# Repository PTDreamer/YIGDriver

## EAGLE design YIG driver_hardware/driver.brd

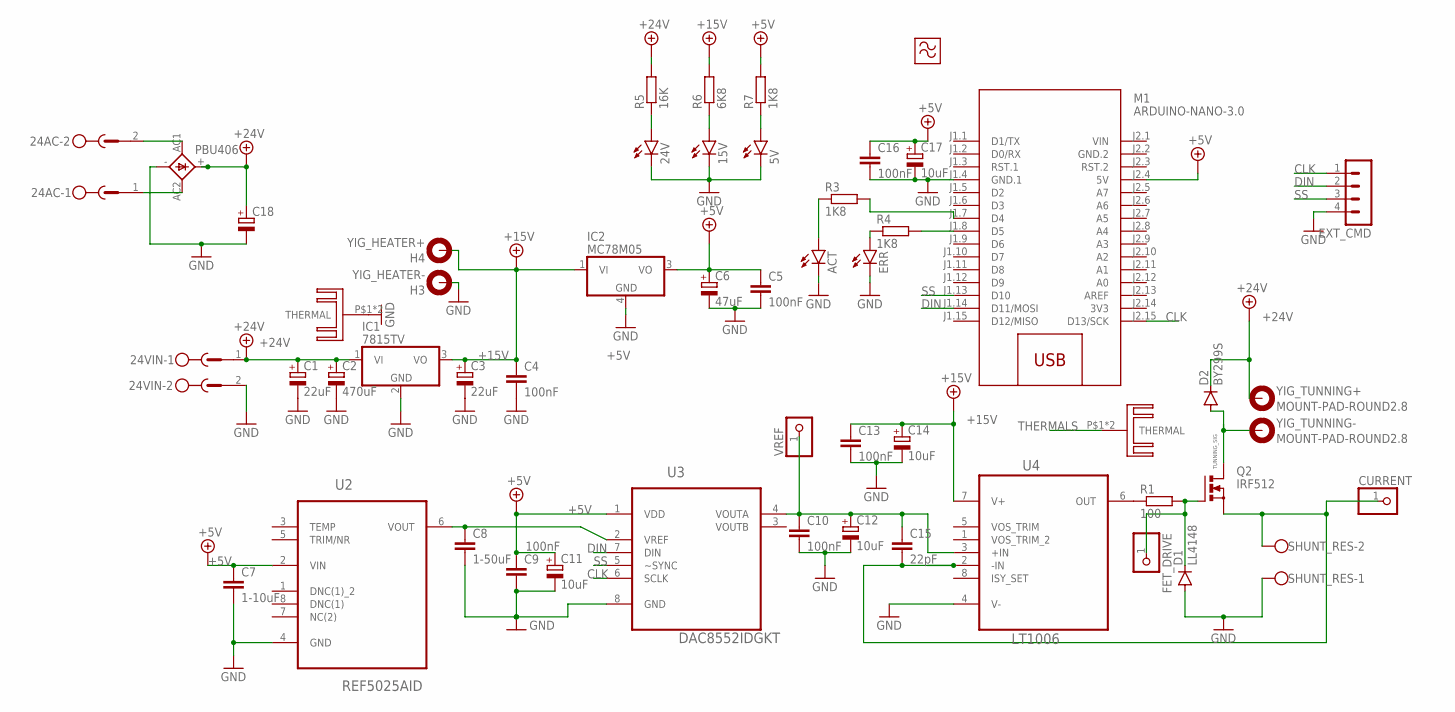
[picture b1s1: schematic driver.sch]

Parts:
5V, 15V, 24V: LEDCHIP-LED0805; CHIP-LED0805
24AC, 24VIN: MSTBV2
ACT: LEDCHIP-LED0805; CHIP-LED0805
C1, C3: 22uF; PANASONIC_E
C2: 470uF; E5-10,5
C4, C13: 100nF; C1210
C5, C9, C10, C16: 100nF; C0603K
C6: 47uF; PANASONIC_D
C7: 1-10uF; C3216
C8: 1-50uF; C3216
C11, C12, C17: 10uF; A/3216-18R
C14: 10uF; E2,5-5
C15: 22pF; C0603
C18: CPOL-EUE7.5-18; E7,5-18
CURRENT: PINHD-1X1; 1X01
D1: LL4148; SOD80C
D2: BY299S; D-10
ERR: LEDCHIP-LED0805; CHIP-LED0805
EXT_CMD: MA04-1
FET_DRIVE: PINHD-1X1; 1X01
H3: YIG_HEATER-; 2,8-PAD
H4: YIG_HEATER+; 2,8-PAD
HEATSYNK: SK09/20V
IC1: 7815TV; TO220V
IC2: MC78M05; DPACK_3
M1: ARDUINO-NANO-3.0
PBU406: 2KBP2KBP_MINE; 2KBP_MINE
Q2: IRF512; TO220BV
R1: 100; M0805
R3, R4, R7: 1K8; M0805
R5: 16K; M0805
R6: 6K8; M0805
SHUNT_RES: W237-102
U2: REF5025AID; SOIC127P600X175-8N
U3: DAC8552IDGKT; SOP65P490X110-8N
U4: LT1006; SOIC127P600X175-8N
U$1: SK09/20V
U$2: YIG_FILTER; EBAY
VREF: PINHD-1X1; 1X01
YIG_TUNNING+: MOUNT-PAD-ROUND2.8; 2,8-PAD
YIG_TUNNING-: MOUNT-PAD-ROUND2.8; 2,8-PAD

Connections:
3V3: M1.J2.14 (3V3)
+5V: C5.1, C6.+, C7.1, C9.1, C11.+, C16.1, C17.+, IC2.3 (VO), M1.J2.4 (5V), R7.2, U2.2 (VIN), U3.1 (VDD)
+15V: C3.+, C4.1, C13.1, C14.+, H4.B2,8, IC1.3 (VO), IC2.1 (VI), R6.2, U4.7 (V+)
+24V: 24VIN.1, C1.+, C2.+, C18.+, D2.C, IC1.1 (VI), PBU406.+, R5.2, YIG_TUNNING+.B2,8
CLK: EXT_CMD.1, M1.J2.15 (D13/SCK), U3.6 (SCLK)
DIN: EXT_CMD.2, M1.J1.14 (D11/MOSI), U3.7 (DIN)
GND: 5V.C, 15V.C, 24V.C, 24VIN.2, ACT.C, C1.-, C2.-, C3.-, C4.2, C5.2, C6.-, C7.2, C8.2, C9.2, C10.2, C11.-, C12.-, C13.2, C14.-, C16.2, C17.-, C18.-, D1.A, ERR.C, EXT_CMD.4, H3.B2,8, HEATSYNK.P$1, HEATSYNK.P$2, IC1.2 (GND), IC2.4 (GND), M1.J1.4 (GND.1), PBU406.-, SHUNT_RES.1, U2.4 (GND), U3.8 (GND), U4.4 (V-)
GND.2: M1.J2.2 (GND.2)
unnamed: C8.1, U2.6 (VOUT), U3.2 (VREF)
unnamed: 24V.A, R5.1
unnamed: C10.1, C12.+, C15.1, U3.4 (VOUTA), U4.3 (+IN), VREF.1
unnamed: 24AC.2, PBU406.AC1
unnamed: R1.1, U4.6 (OUT)
unnamed: D1.C, FET_DRIVE.1, Q2.G, R1.2
unnamed: C15.2, CURRENT.1, Q2.S, SHUNT_RES.2, U4.2 (-IN)
unnamed: 15V.A, R6.1
unnamed: 5V.A, R7.1
unnamed: M1.J1.7 (D4), R3.2
unnamed: M1.J1.8 (D5), R4.2
unnamed: ERR.A, R4.1
unnamed: ACT.A, R3.1
unnamed: 24AC.1, PBU406.AC2
SS: EXT_CMD.3, M1.J1.13 (D10), U3.5 (~SYNC)
THERMALS: U$1.P$1, U$1.P$2
TUNNING_SIG: D2.A, Q2.D, YIG_TUNNING-.B2,8
VIN: M1.J2.1 (VIN)

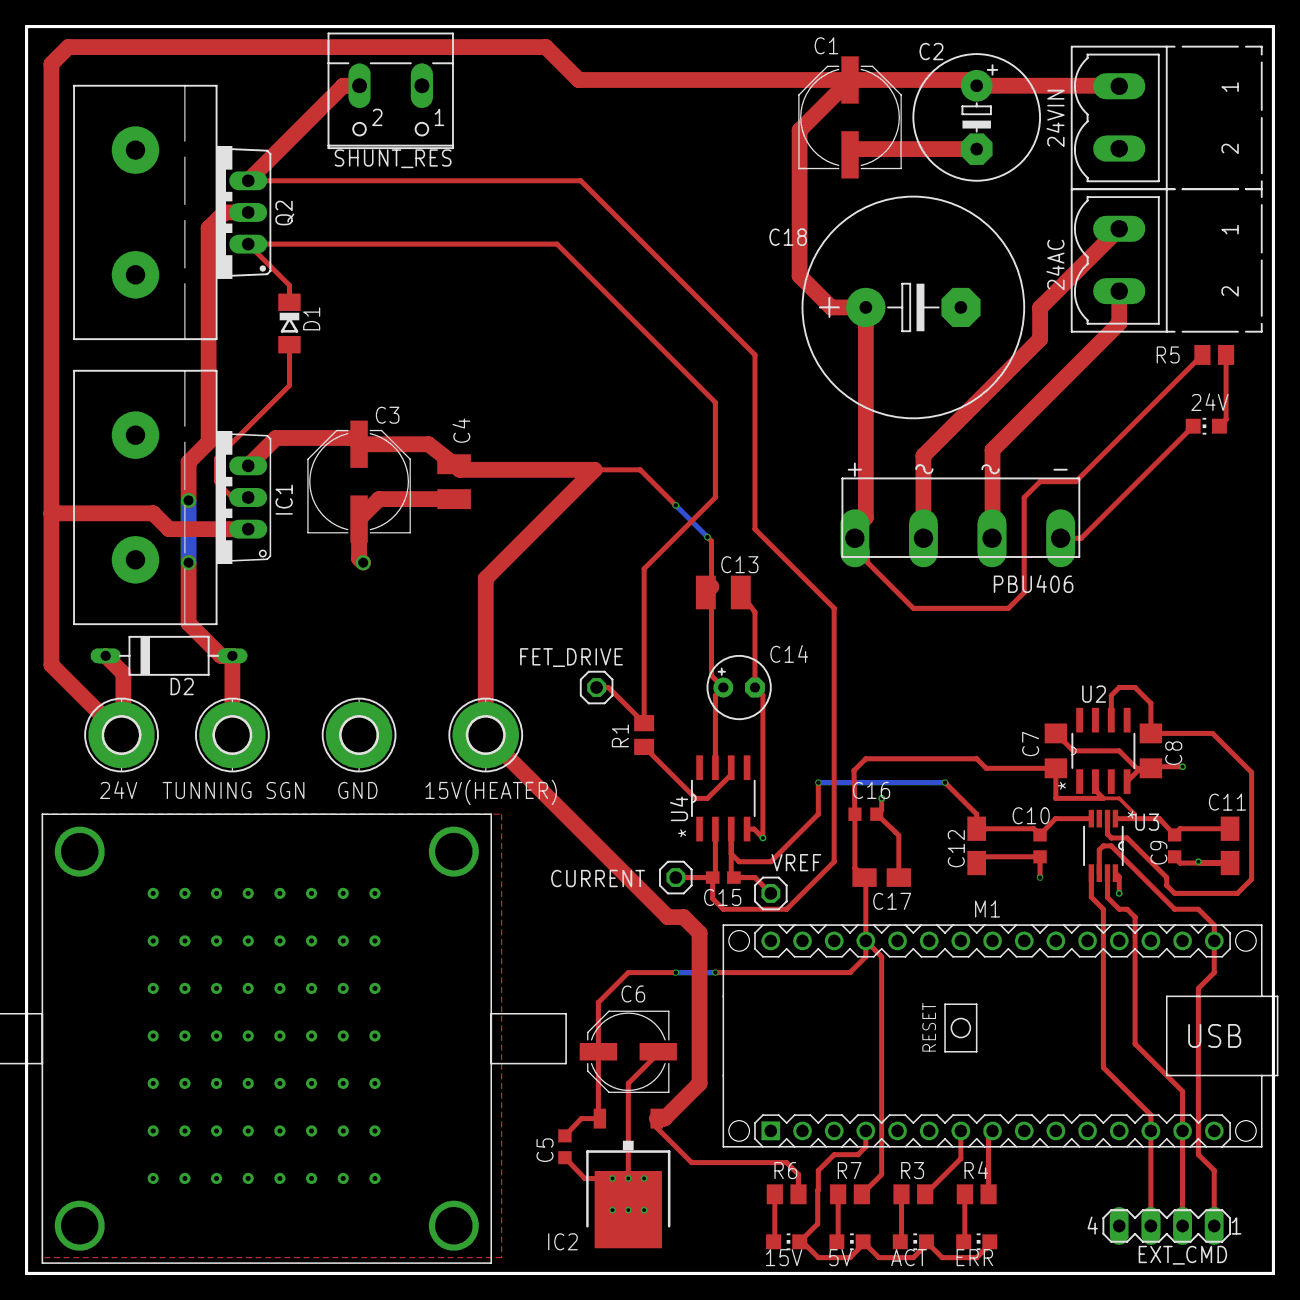
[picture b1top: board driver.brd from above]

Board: 2 copper layers, 100.0 x 100.0 mm, 53 parts (0 on the bottom side), 23 nets.

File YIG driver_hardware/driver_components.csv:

"Qty";"Value";"Device";"Package";"Parts";"Description";"MF";"MPN";"OC_FARNELL";"OC_NEWARK";"PACKAGE";"POPULARITY";"SPICEPREFIX";"SUPPLIER";
"1";"";"2KBP2KBP_MINE";"2KBP_MINE";"B1";"RECTIFIER";"";"";"";"";"";"";"";"";
"1";"";"CPOL-EUE10-20";"EB20D";"C18";"POLARIZED CAPACITOR, European symbol";"";"";"";"";"";"0";"C";"";
"5";"";"LEDCHIP-LED0805";"CHIP-LED0805";"5V, 15V, 24V, ACT, ERR";"LED";"";"";"";"";"";"68";"";"";
"1";"";"MA04-1";"MA04-1";"EXT_CMD";"PIN HEADER";"";"";"unknown";"unknown";"";"41";"";"";
"2";"";"MSTBV2";"MSTBV2";"24AC, 24VIN";"PHOENIX";"";"";"unknown";"unknown";"";"3";"";"";
"2";"";"SK09/20V";"SK09/20V";"HEATSYNK, U$1";"";"";"";"";"";"";"";"";"";
"1";"";"W237-102";"W237-102";"SHUNT_RES";"WAGO SCREW CLAMP";"";"237-102";"unknown";"70K9898";"";"32";"";"";
"1";"1-10uF";"C-EUC3216";"C3216";"C7";"CAPACITOR, European symbol";"";"";"";"";"";"4";"C";"";
"1";"1-50uF";"C-EUC3216";"C3216";"C8";"CAPACITOR, European symbol";"";"";"";"";"";"4";"C";"";
"1";"100";"R-EU_M0805";"M0805";"R1";"RESISTOR, European symbol";"";"";"";"";"";"45";"R";"";
"6";"100nF";"C-EUC0805";"C0805";"C4, C5, C9, C10, C13, C16";"CAPACITOR, European symbol";"";"";"";"";"";"88";"C";"";
"2";"10uF";"CPOL-EUA/3216-18R";"A/3216-18R";"C11, C12";"POLARIZED CAPACITOR, European symbol";"";"";"";"";"";"1";"C";"";
"1";"10uF";"CPOL-EUCT3216";"CT3216";"C17";"POLARIZED CAPACITOR, European symbol";"";"";"";"";"";"1";"C";"";
"1";"10uF";"CPOL-EUE";"PANASONIC_E";"C14";"POLARIZED CAPACITOR, European symbol";"";"";"";"";"";"0";"C";"";
"1";"12K";"R-EU_M0805";"M0805";"R5";"RESISTOR, European symbol";"";"";"";"";"";"";"";"";
"3";"1K8";"R-EU_M0805";"M0805";"R3, R4, R7";"RESISTOR, European symbol";"";"";"";"";"";"";"";"";
"1";"1N4148";"1N4148DO35-7";"DO35-7";"D1";"DIODE";"";"";"";"";"";"58";"";"";
"1";"1n4007";"CGRM4007-G";"SOD-123_MINI-SMA";"D2";"Molded plasitc,JEDEC SOD-123/Mini SMA";"";"";"";"";"";"0";"";"";
"1";"22pF";"C-EUC0603";"C0603";"C15";"CAPACITOR, European symbol";"";"";"";"";"";"73";"C";"";
"2";"22uF";"CPOL-EUE";"PANASONIC_E";"C1, C3";"POLARIZED CAPACITOR, European symbol";"";"";"";"";"";"0";"C";"";
"1";"470uF";"CPOL-EUE5-10.5";"E5-10,5";"C2";"POLARIZED CAPACITOR, European symbol";"";"";"";"";"";"23";"C";"";
"1";"47uF";"CPOL-EUD";"PANASONIC_D";"C6";"POLARIZED CAPACITOR, European symbol";"";"";"";"";"";"16";"C";"";
"1";"6K8";"R-EU_M0805";"M0805";"R6";"RESISTOR, European symbol";"";"";"";"";"";"";"";"";
"1";"7815TV";"7815TV";"TO220V";"IC1";"Positive VOLTAGE REGULATOR";"";"";"";"";"";"0";"";"";
"1";"ARDUINO-NANO-3.0";"ARDUINO-NANO-3.0";"ARDUINO-NANO-3.0";"M1";"Arduino Nano 3.0 and compatible devices";"";"";"";"";"";"";"";"";
"1";"DAC8552IDGKT";"DAC8552IDGKT";"SOP65P490X110-8N";"U3";"0.05ìV/°C max, SINGLE-SUPPLY CMOS OPERATIONAL AMPLIFIERS Zer.-Drift Series";"";"DAC8552IDGKT";"-";"06M7244";"MSOP-8";"";"";"Texas Instruments";
"1";"IRF512";"IRF512";"TO220BV";"Q2";"N-CHANNEL MOS FET";"";"";"";"";"";"3";"";"";
"1";"LT1006";"LT1006S8PBF";"SOIC127P600X175-8N";"U4";"Precision, Single Supply Op Amp";"";"LT1006S8#PBF";"9559230";"57M0724";"SOIC-8";"";"";"Linear Technology";
"1";"MC78M05";"MC78M05CDTG";"DPACK_3";"IC2";"500 mA Positive Voltage Regulators";"";"";"";"";"";"0";"";"";
"4";"MOUNT-PAD-ROUND2.8";"MOUNT-PAD-ROUND2.8";"2,8-PAD";"H1, H2, H3, H4";"MOUNTING PAD, round";"";"";"";"";"";"6";"";"";
"1";"REF5025AID";"REF5025AID";"SOIC127P600X175-8N";"U2";"Low-Noise, Very Low Drift, Precision VOLTAGE REFERENCE";"";"REF5025AID";"1439622";"50M8895";"SOIC-8";"";"";"Texas Instruments";
"1";"YIG_FILTER";"YIG_FILTER";"EBAY";"U$2";"";"";"";"";"";"";"";"";"";

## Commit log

2021-09-11 Add license

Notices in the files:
parts and their libraries:
diy-modules: Released under the Creative Commons Attribution 4.0 International License: http://creativecommons.org/licenses/by/4.0
